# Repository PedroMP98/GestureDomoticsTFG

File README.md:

# GestureDomoticsTFG
In this repository, you can find the code related to my Bachelor's Thesis (TFG) concerning the home automation control of any household element using the gesture sensors APDS-9960 and SkyWriter 3D

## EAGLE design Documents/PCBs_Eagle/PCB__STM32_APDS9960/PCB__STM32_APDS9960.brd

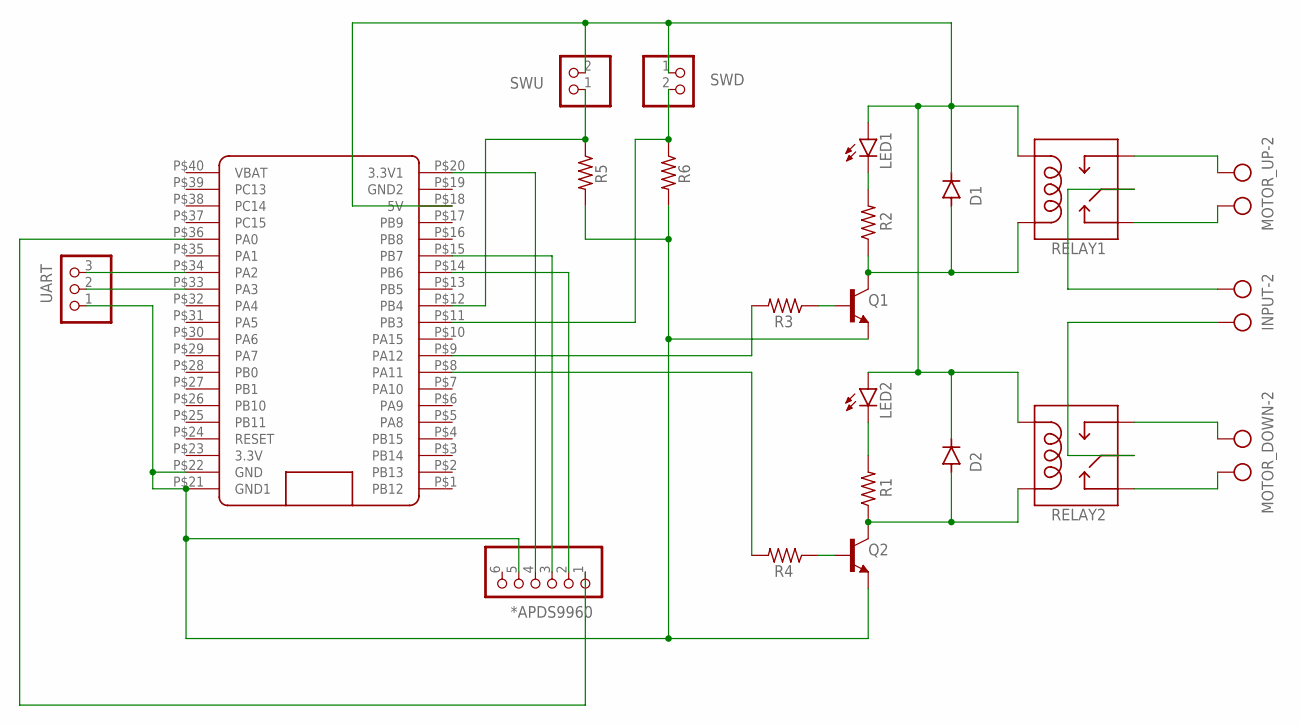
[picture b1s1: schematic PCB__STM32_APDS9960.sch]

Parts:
*APDS9960: PINHD-1X6; 1X06
D1, D2: 1N4446; DO35-10
INPUT: AK500/2
LED1, LED2: TLLR4400; LED3MM
MOTOR_DOWN: AK500/2
MOTOR_UP: AK500/2
Q1, Q2: 2N3904; TO92
R1, R2, R3, R4, R5, R6: R-US_0207/10; 0207/10
RELAY1, RELAY2: RELAYPTH; SRD-05VDC-SL-C
SWD: PINHD-1X2; 1X02
SWU: PINHD-1X2; 1X02
U$1: BLUE_PILL
UART: PINHD-1X3; 1X03

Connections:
unnamed: R5.1, SWU.1, U$1.P$12 (PB4)
unnamed: R6.1, SWD.2, U$1.P$11 (PB3)
unnamed: D1.C, D2.C, LED1.A, LED2.A, RELAY1.COIL0, RELAY2.COIL0, SWD.1, SWU.2, U$1.P$18 (5V)
unnamed: R4.2, U$1.P$8 (PA11)
unnamed: LED2.K (C), R1.2
unnamed: D2.A, Q2.1 (C), R1.1, RELAY2.COIL1
unnamed: MOTOR_DOWN.2, RELAY2.SWOPEN
unnamed: MOTOR_DOWN.1, RELAY2.SWCLOSED (SWCLOSE)
unnamed: INPUT.1, RELAY2.SWCOMMON
unnamed: INPUT.2, RELAY1.SWCOMMON
unnamed: MOTOR_UP.2, RELAY1.SWOPEN
unnamed: MOTOR_UP.1, RELAY1.SWCLOSED (SWCLOSE)
unnamed: R3.2, U$1.P$9 (PA12)
unnamed: LED1.K (C), R2.2
unnamed: D1.A, Q1.1 (C), R2.1, RELAY1.COIL1
unnamed: Q2.2 (B), R4.1
unnamed: Q1.2 (B), R3.1
unnamed: U$1.P$34 (PA2), UART.3
unnamed: *APDS9960.4, U$1.P$20 (3.3V1)
unnamed: U$1.P$33 (PA3), UART.2
unnamed: *APDS9960.2, U$1.P$14 (PB6)
unnamed: *APDS9960.1, U$1.P$36 (PA0)
unnamed: *APDS9960.3, U$1.P$15 (PB7)
unnamed: *APDS9960.5, Q1.3 (E), Q2.3 (E), R5.2, R6.2, U$1.P$21 (GND1), U$1.P$22 (GND), UART.1

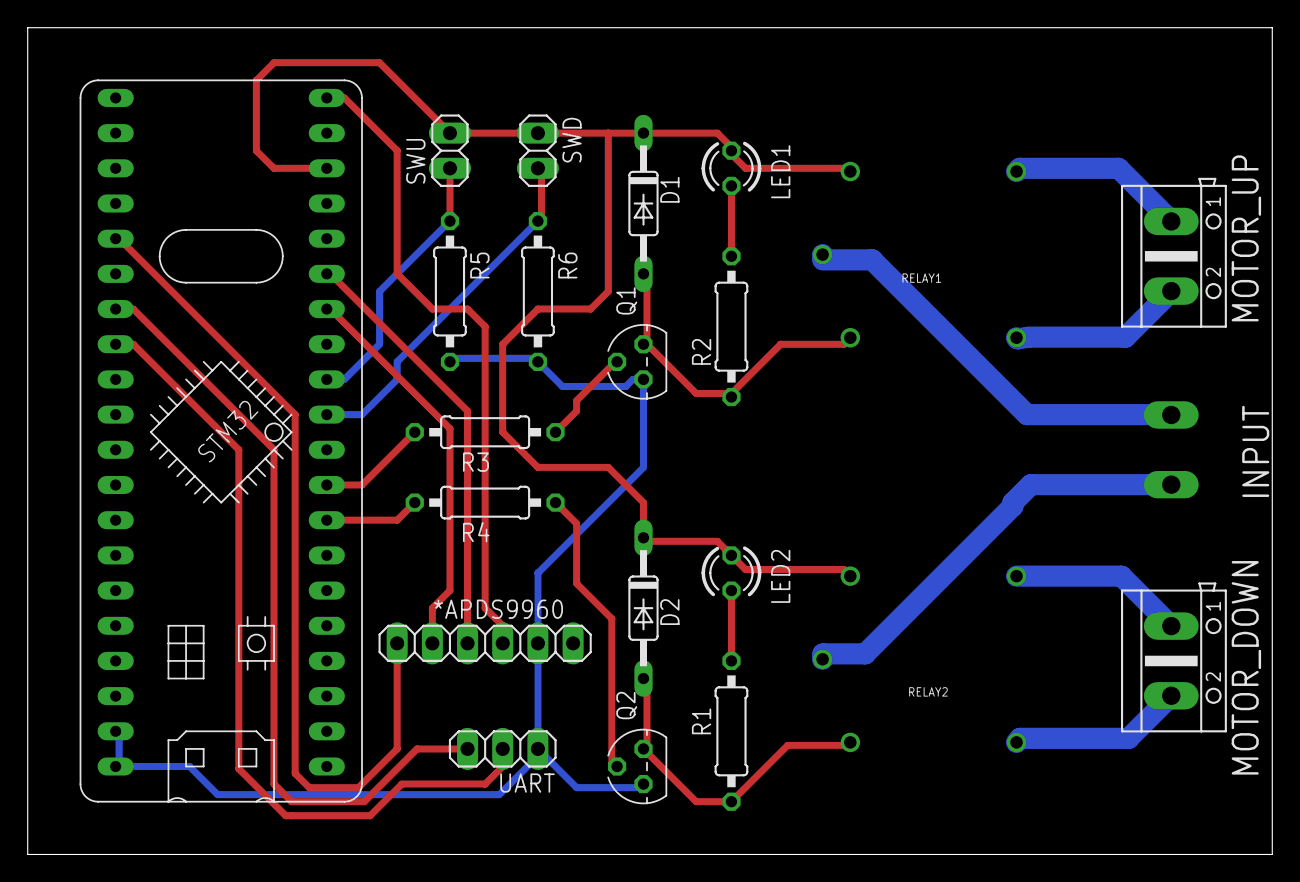
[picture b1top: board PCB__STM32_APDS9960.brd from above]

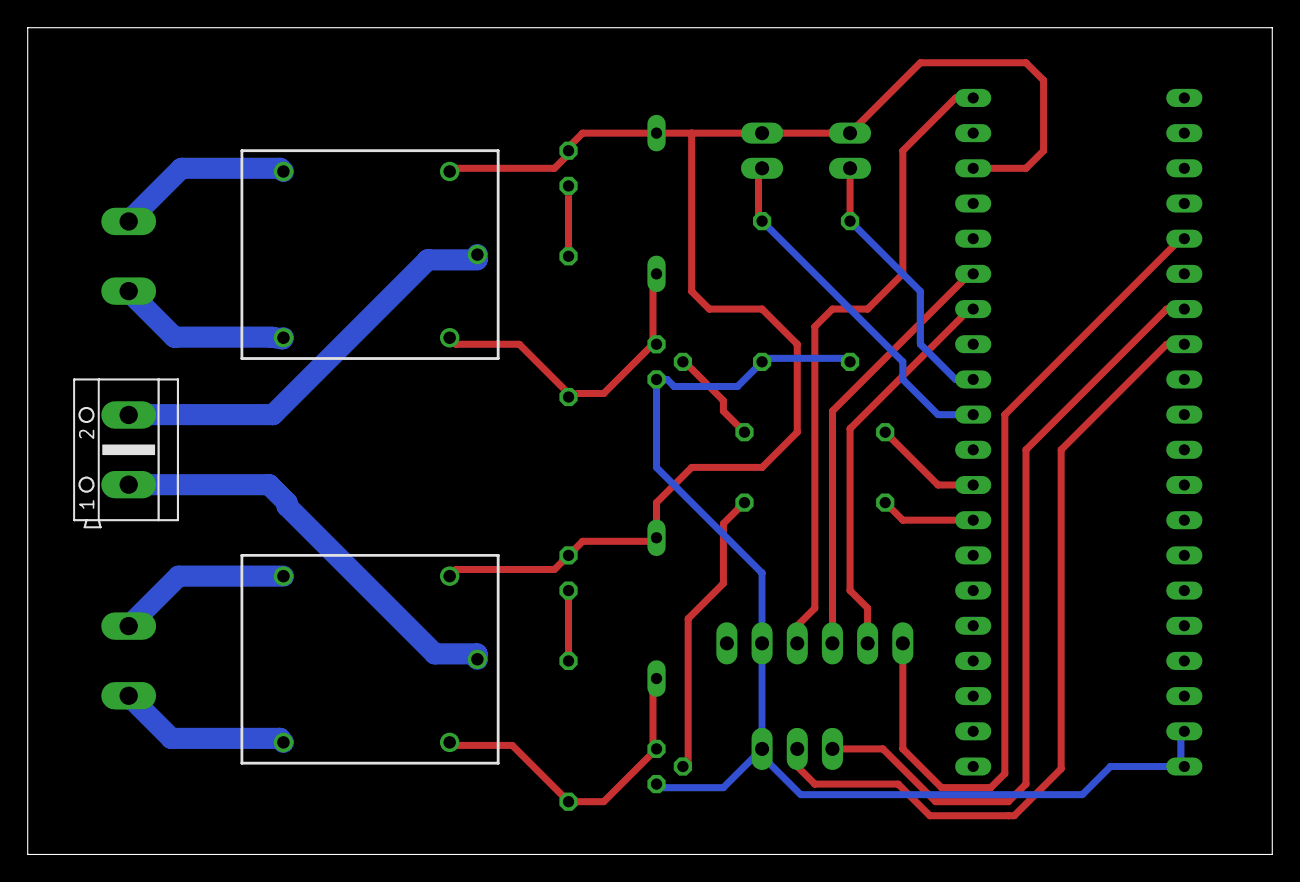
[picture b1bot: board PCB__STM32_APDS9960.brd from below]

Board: 2 copper layers, 89.8 x 59.7 mm, 22 parts (3 on the bottom side), 24 nets.

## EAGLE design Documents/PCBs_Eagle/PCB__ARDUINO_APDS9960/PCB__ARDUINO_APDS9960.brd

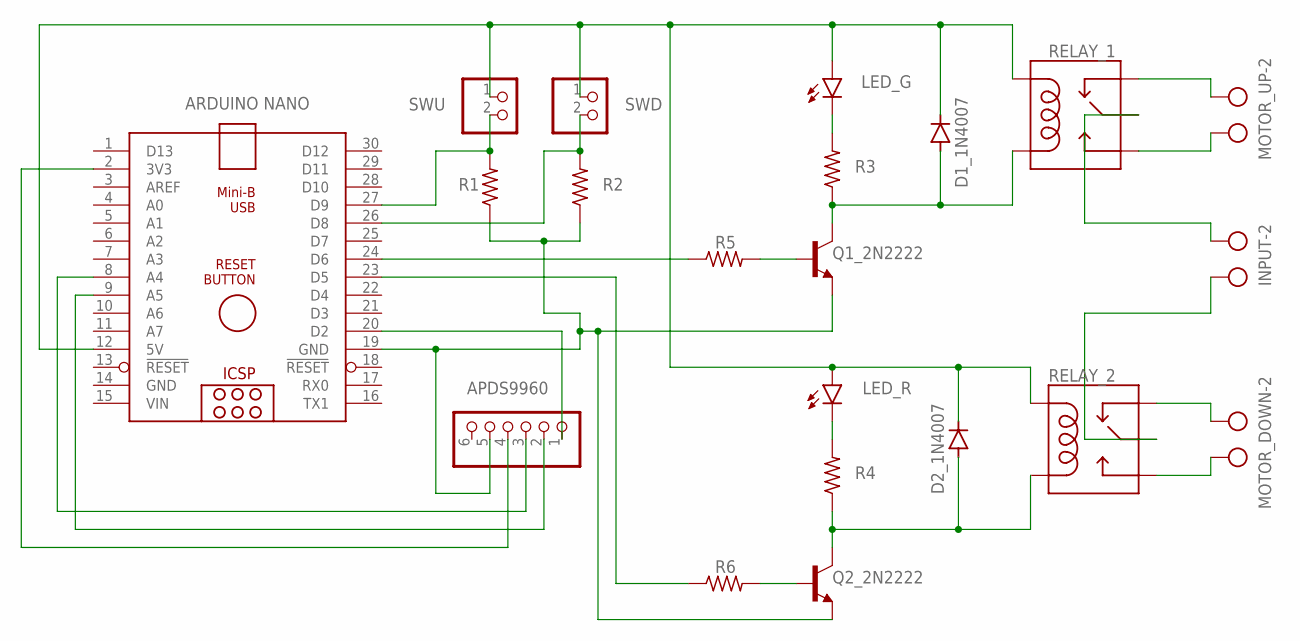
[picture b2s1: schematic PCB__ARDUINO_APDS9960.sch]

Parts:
APDS9960: PINHD-1X6; 1X06
ARDUINO_NANO: ARDUINO NANO; ARDUINO_NANO
D1_1N4007, D2_1N4007: 1N4446; DO35-10
INPUT: AK500/2
LED_G: TLLY4400; LED3MM
LED_R: TLLY4400; LED3MM
MOTOR_DOWN: AK500/2
MOTOR_UP: AK500/2
Q1_2N2222, Q2_2N2222: 2N3904; TO92
R1, R2, R3, R4, R5, R6: R-US_0207/10; 0207/10
RELAY_1, RELAY_2: RELAYPTH; SRD-05VDC-SL-C
SWD: PINHD-1X2; 1X02
SWU: PINHD-1X2; 1X02

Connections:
GND: ARDUINO_NANO.14 (GND)
unnamed: D1_1N4007.A, Q1_2N2222.1 (C), R3.1, RELAY_1.COIL0
unnamed: LED_G.K (C), R3.2
unnamed: ARDUINO_NANO.27 (D9), R1.2, SWU.2
unnamed: ARDUINO_NANO.12 (5V), D1_1N4007.C, D2_1N4007.C, LED_G.A, LED_R.A, RELAY_1.COIL1, RELAY_2.COIL1, SWD.1, SWU.1
unnamed: LED_R.K (C), R4.2
unnamed: D2_1N4007.A, Q2_2N2222.1 (C), R4.1, RELAY_2.COIL0
unnamed: Q1_2N2222.2 (B), R5.2
unnamed: Q2_2N2222.2 (B), R6.2
unnamed: ARDUINO_NANO.24 (D6), R5.1
unnamed: MOTOR_DOWN.2, RELAY_2.SWCLOSED (SWCLOSE)
unnamed: APDS9960.1, ARDUINO_NANO.20 (D2)
unnamed: APDS9960.4, ARDUINO_NANO.2 (3V3)
unnamed: APDS9960.2, ARDUINO_NANO.9 (A5)
unnamed: APDS9960.3, ARDUINO_NANO.8 (A4)
unnamed: ARDUINO_NANO.26 (D8), R2.2, SWD.2
unnamed: MOTOR_DOWN.1, RELAY_2.SWOPEN
unnamed: ARDUINO_NANO.23 (D5), R6.1
unnamed: APDS9960.5, ARDUINO_NANO.19 (GND), Q1_2N2222.3 (E), Q2_2N2222.3 (E), R1.1, R2.1
unnamed: INPUT.1, RELAY_2.SWCOMMON
unnamed: INPUT.2, RELAY_1.SWCOMMON
unnamed: MOTOR_UP.2, RELAY_1.SWCLOSED (SWCLOSE)
unnamed: MOTOR_UP.1, RELAY_1.SWOPEN
VIN: ARDUINO_NANO.15 (VIN)

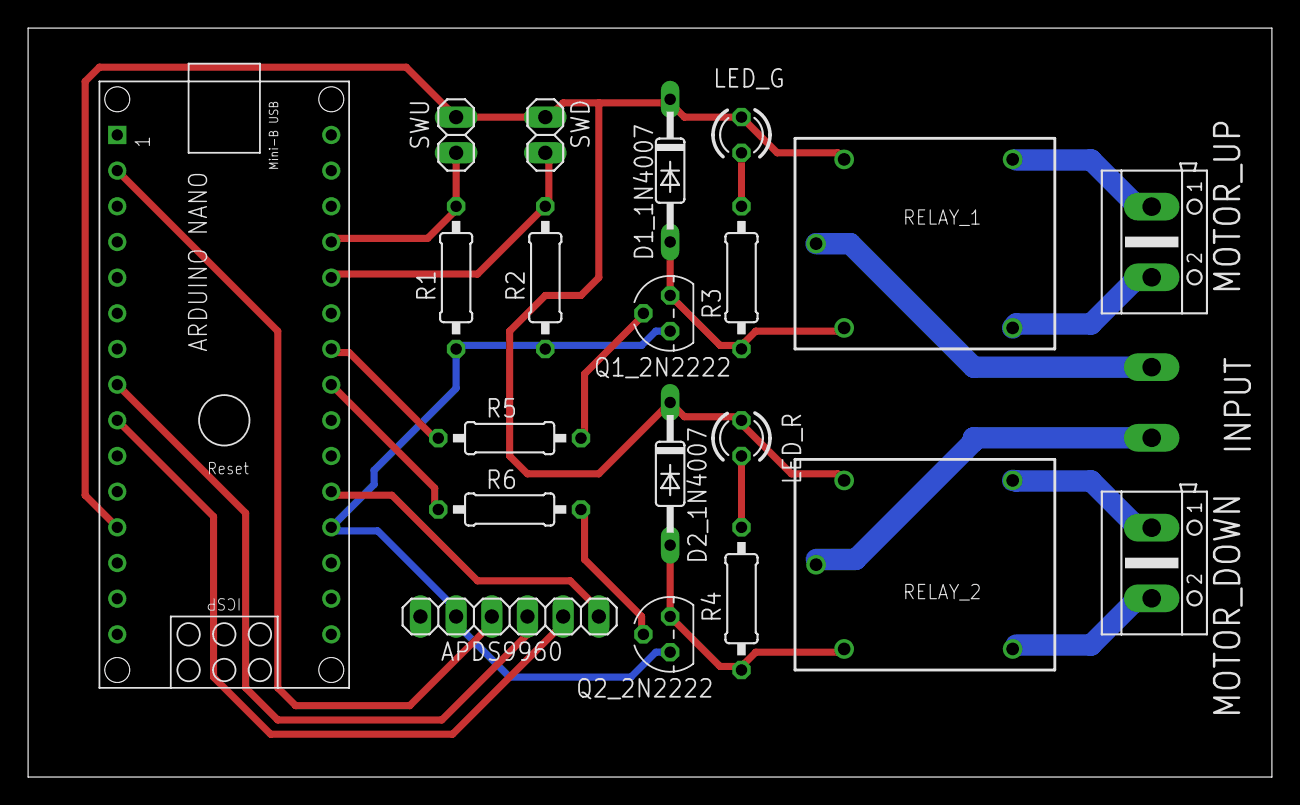
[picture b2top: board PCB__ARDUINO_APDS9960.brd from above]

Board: 2 copper layers, 88.6 x 53.3 mm, 21 parts (1 on the bottom side), 22 nets.

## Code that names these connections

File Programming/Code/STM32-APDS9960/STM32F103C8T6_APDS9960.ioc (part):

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Mcu.Name=STM32F103C(8-B)Tx
Mcu.Package=LQFP48
Mcu.UserName=STM32F103C8Tx
PA0-WKUP.GPIOParameters=GPIO_ModeDefaultEXTI
PA0-WKUP.GPIO_ModeDefaultEXTI=GPIO_MODE_IT_FALLING
PA0-WKUP.Signal=GPXTI0
PA11.GPIOParameters=PinState
PA11.PinState=GPIO_PIN_RESET
PA11.Signal=GPIO_Output
PA12.GPIOParameters=PinState
PA12.PinState=GPIO_PIN_RESET
PA12.Signal=GPIO_Output
PA13.Mode=Serial_Wire
PA13.Signal=SYS_JTMS-SWDIO
PA14.Mode=Serial_Wire
PA14.Signal=SYS_JTCK-SWCLK
PA2.Mode=Asynchronous
PA2.Signal=USART2_TX
PA3.Mode=Asynchronous
PA3.Signal=USART2_RX
PB3.Signal=GPIO_Input
PB4.Signal=GPIO_Input
PB6.Mode=I2C
PB6.Signal=I2C1_SCL
PB7.Mode=I2C
PB7.Signal=I2C1_SDA
PD0-OSC_IN.Mode=HSE-External-Oscillator
PD0-OSC_IN.Signal=RCC_OSC_IN
PD1-OSC_OUT.Mode=HSE-External-Oscillator
PD1-OSC_OUT.Signal=RCC_OSC_OUT
RCC.SYSCLKFreq_VALUE=72000000
RCC.SYSCLKSource=RCC_SYSCLKSOURCE_PLLCLK
board=custom

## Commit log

2023-09-03 Add files via upload
    Documents of the project
2023-09-03 Documents of the project
2023-09-03 Uploaded libraries
2023-11-16 PCB files created with Autodesk Eagle
2023-11-30 Programa para el control del sensor SkyWriter 3D
2023-12-18 Programa para el control del sensor APDS-9960
